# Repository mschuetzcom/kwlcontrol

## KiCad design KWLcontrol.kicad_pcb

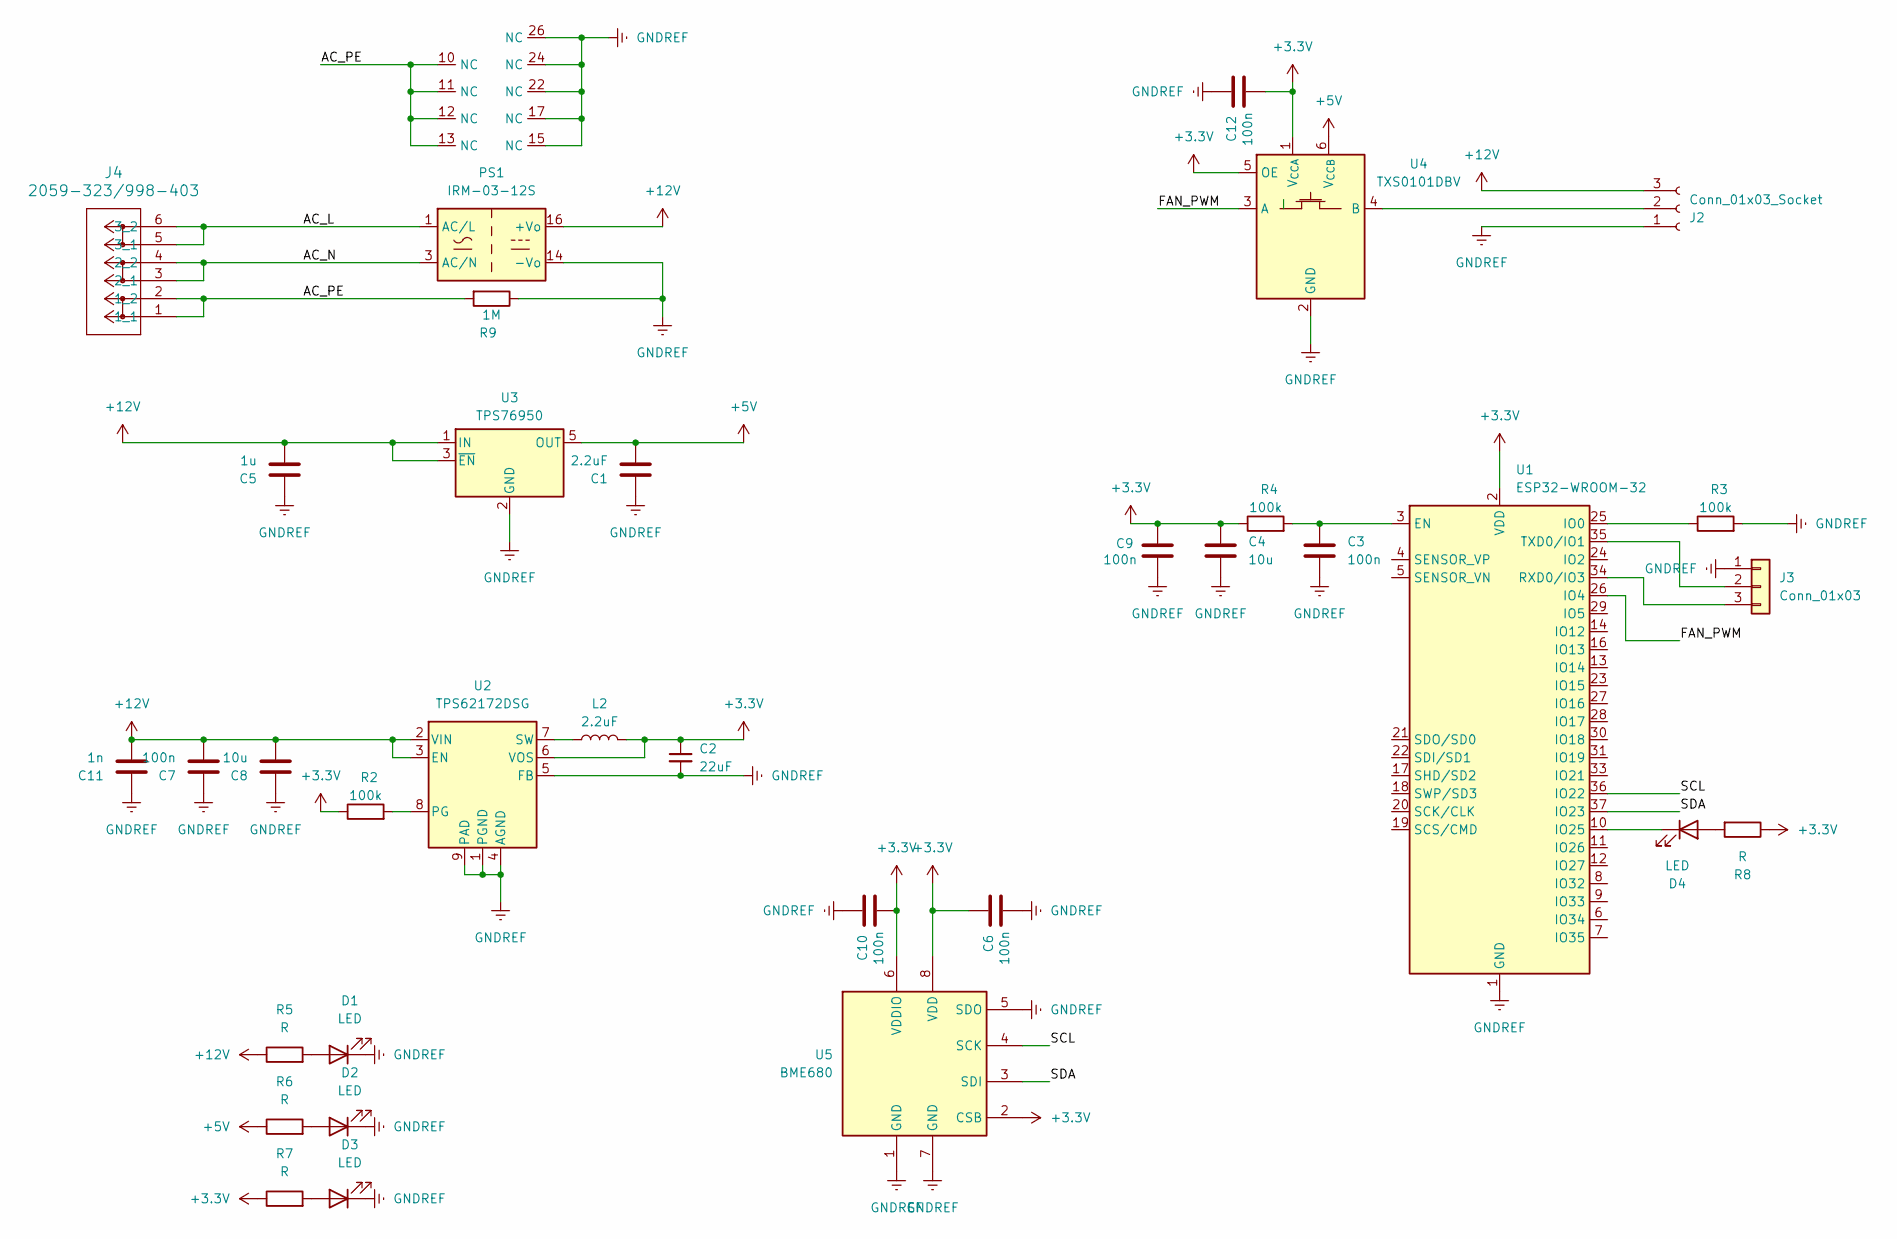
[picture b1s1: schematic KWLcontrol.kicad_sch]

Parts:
C1: 2.2uF; C_0805_2012Metric_Pad1.18x1.45mm_HandSolder
C2: 22uF; C_0805_2012Metric_Pad1.18x1.45mm_HandSolder
C3, C9: 100n; C_0603_1608Metric_Pad1.08x0.95mm_HandSolder
C4: 10u; C_0603_1608Metric_Pad1.08x0.95mm_HandSolder
C5: 1u; C_0805_2012Metric_Pad1.18x1.45mm_HandSolder
C6, C7, C10, C12: 100n; C_0805_2012Metric_Pad1.18x1.45mm_HandSolder
C8: 10u; C_0805_2012Metric_Pad1.18x1.45mm_HandSolder
C11: 1n; C_0805_2012Metric_Pad1.18x1.45mm_HandSolder
D1, D2, D3, D4: LED; LED_0603_1608Metric_Pad1.05x0.95mm_HandSolder
J2: Conn_01x03_Socket; PhoenixContact_MC_1,5_3-G-3.81_1x03_P3.81mm_Horizontal
J3: Conn_01x03; PinHeader_1x03_P1.00mm_Vertical
J4: 2059-323/998-403; CONN3_2059-323&slash_998-403_WAG
L2: 2.2uF; L_0805_2012Metric_Pad1.15x1.40mm_HandSolder
PS1: IRM-03-12S; Converter_ACDC_MeanWell_IRM-03-xx_SMD
R2, R3: 100k; R_0805_2012Metric_Pad1.20x1.40mm_HandSolder
R4: 100k; R_0603_1608Metric_Pad0.98x0.95mm_HandSolder
R5, R6, R7, R8: R; R_0603_1608Metric_Pad0.98x0.95mm_HandSolder
R9: 1M; R_0805_2012Metric_Pad1.20x1.40mm_HandSolder
U1: ESP32-WROOM-32
U2: TPS62172DSG; WSON-8-1EP_2x2mm_P0.5mm_EP0.9x1.6mm_ThermalVias
U3: TPS76950; SOT-23-5
U4: TXS0101DBV; SOT-23-6
U5: BME680; Bosch_LGA-8_3x3mm_P0.8mm_ClockwisePinNumbering

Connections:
+3.3V: C2.1, C4.1, C6.2, C9.2, C10.1, C12.1, L2.2, R2.1, R4.1, R7.1, R8.1, U1.2 (VDD), U2.6 (VOS), U4.1 (V_{CCA}), U4.5 (OE), U5.2 (CSB), U5.6 (VDDIO), U5.8 (VDD)
+5V: C1.2, R6.1, U3.5 (OUT), U4.6 (V_{CCB})
+12V: C5.2, C7.2, C8.2, C11.2, J2.3, PS1.16 (+Vo), R5.1, U2.2 (VIN), U2.3 (EN), U3.1 (IN), U3.3 (~EN)
/AC_L: J4.5 (3_1), J4.6 (3_2), PS1.1 (AC/L)
/AC_N: J4.3 (2_1), J4.4 (2_2), PS1.3 (AC/N)
/AC_PE: J4.1 (1_1), J4.2 (1_2), PS1.10 (NC), PS1.11 (NC), PS1.12 (NC), PS1.13 (NC), R9.2
/FAN_PWM: U1.26 (IO4), U4.3 (A)
/SCL: U1.36 (IO22), U5.4 (SCK)
/SDA: U1.37 (IO23), U5.3 (SDI)
GNDREF: C1.1, C2.2, C3.2, C4.2, C5.1, C6.1, C7.1, C8.1, C9.1, C10.2, C11.1, C12.2, D1.1 (K), D2.1 (K), D3.1 (K), J2.1, J3.1, PS1.14 (-Vo), PS1.15 (NC), PS1.17 (NC), PS1.22 (NC), PS1.24 (NC), PS1.26 (NC), R3.2, R9.1, U1.1 (GND), U1.15 (GND), U1.38 (GND), U1.39 (GND), U2.1 (PGND), U2.4 (AGND), U2.5 (FB), U2.9 (PAD), U3.2 (GND), U4.2 (GND), U5.1 (GND), U5.5 (SDO), U5.7 (GND)
unnamed: D1.2 (A), R5.2
unnamed: D2.2 (A), R6.2
unnamed: D3.2 (A), R7.2
unnamed: D4.2 (A), R8.2
unnamed: D4.1 (K), U1.10 (IO25)
unnamed: J2.2, U4.4 (B)
unnamed: J3.2, U1.35 (TXD0/IO1)
unnamed: J3.3, U1.34 (RXD0/IO3)
unnamed: C3.1, R4.2, U1.3 (EN)
unnamed: R3.1, U1.25 (IO0)
unnamed: R2.2, U2.8 (PG)
unnamed: L2.1, U2.7 (SW)

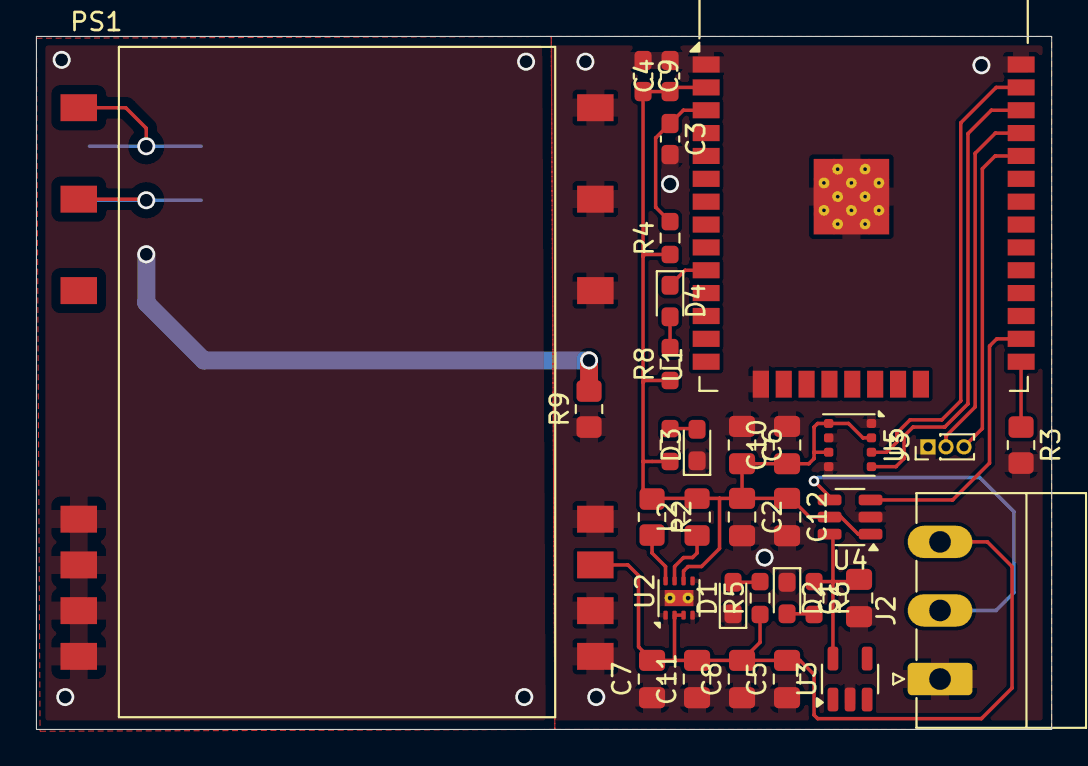
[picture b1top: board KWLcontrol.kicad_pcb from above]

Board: 2 copper layers, 56.4 x 38.5 mm, 34 parts (1 on the bottom side), 22 nets.

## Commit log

2025-02-11 initial commit of current state
2025-02-11 add gitignore
2025-02-11 new connectors, some silkscreen
2025-02-11 add missing local footprint library
2025-02-11 finished v1, exported and ordered
2025-02-13 add digikey basket
2025-02-13 add readme.md and images
2025-02-13 more images
2025-02-13 minor changes and improvements
2025-02-13 3D images
2025-02-17 improvements, add BME680
2025-02-17 add esphome yaml file
